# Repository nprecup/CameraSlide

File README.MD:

Automated Camera Slider
=================================================

The goal of this project is to create a budget, yet high quality, motorized camera slider, with two axis capability, and Bluetooth communications. This slider is to be used in very remote locations for time-lapse landscape astrophotography. This drives a requirement for portability, with a small battery and low power consumption.

Mechanical Design
-----------------------

The slide axis is made using two aluminum shafts that serve as rails. A low cost ACME lead screw moves the cart along the axis, driven by a low cost Futaba S3003 servo modified for continuous rotation. The controller can be adapted (without modification to the circuit) for other mechanical drive systems that may be more practical depending on the resources available, including belts or driven rollers. The choice of using hobby servos instead of stepper motors was made clear by the power consumption and complexity requirement. Complex motion profiles are not necessary, and open loop control will work fine. Stepper motors consume too much current, all the time (though the current can be reduced while not moving). Servo motors already have drivers built into them, making it necessary to supply only power and PWM control input. While the open loop control is based upon dead reckoning (timing), rather than by the advantageous simple steps of a stepper motor, the motors can be moved carefully to produce repeatable results. A stepper motor requires additional drive circuitry, increasing cost and complexity.

Circuit Design
-----------------------

This project uses a BlueGiga BLE112 module to control and interface with a motorized camera slide. The BLE112 module contains a 2541 microcontroller that is capable of providing 16-bit resolution PWM output for servo drive signals, hardware interrupt events for limit switches, and timers with GPIO to trigger a camera shutter for time lapse photography. The system is currently being developed for Canon EOS cameras, with an Android app for bluetooth control.

The circuit was designed using Eagle PCB design software. The schematic and board files are located in the repository and may be ordered through any PCB fab shop that can handle Eagle .brd files. Below is the schematic of the circuit.

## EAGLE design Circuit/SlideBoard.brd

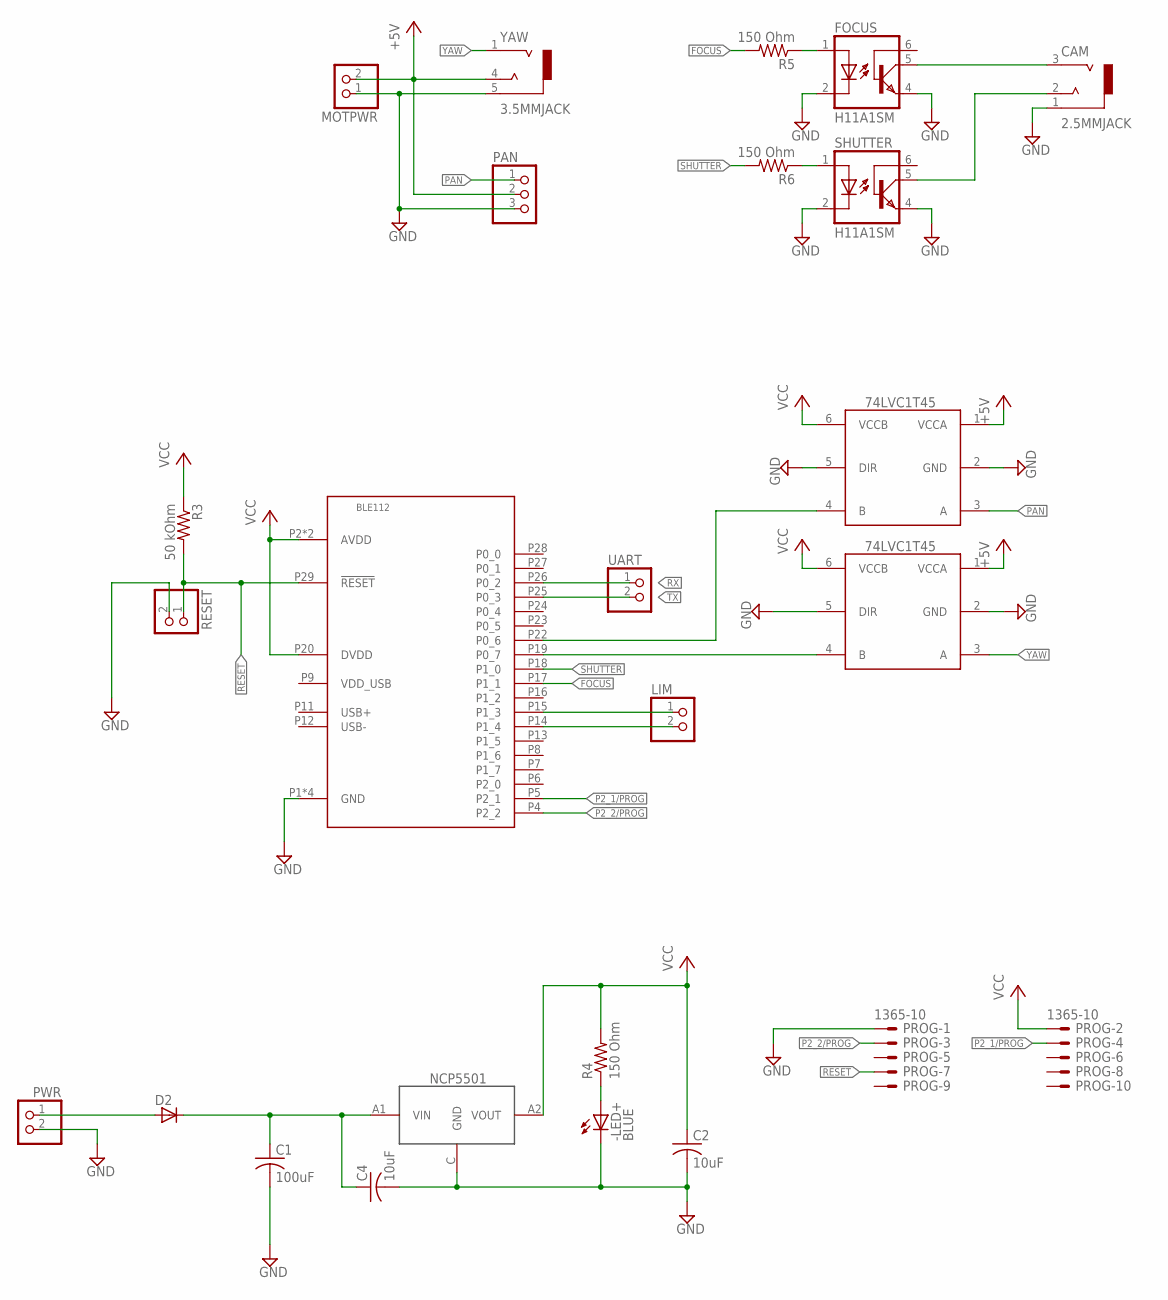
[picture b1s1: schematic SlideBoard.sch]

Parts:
-LED+: BLUE; CHIP-LED0603
C1: 100uF; C1210
C2, C4: 10uF; C0805
CAM: 2.5MMJACK
D2: D-A1-C3; SOT23
FOCUS: H11A1SM; DIL6-SMD
LIM: PINHD-1X2; 1X02
MOTPWR: PINHD-1X2; 1X02
PAN: PINHD-1X3; 1X03
PROG: 1365-10
PWR: PINHD-1X2; 1X02
R3: 50 kOhm; R0603
R4, R5, R6: 150 Ohm; R0402
RESET: PINHD-1X2; 1X02
SHUTTER: H11A1SM; DIL6-SMD
U$1: BLE112
U$2, U$4: 741T45; SOT363_PHILIPS
U$3: NCP5501; DPACK_3
UART: PINHD-1X2; 1X02
YAW: 3.5MMJACK; 35RA_SMT

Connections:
+5V: MOTPWR.2, PAN.2, U$2.1 (VCCA), U$4.1 (VCCA), YAW.4
FOCUS: R5.2, U$1.P17 (P1_1)
GND: -LED+.C, C1.2, C2.2, C4.2, CAM.1 (5-GND), FOCUS.2 (C), FOCUS.4 (EMI), MOTPWR.1, PAN.3, PROG.1, PWR.2, RESET.2, SHUTTER.2 (C), SHUTTER.4 (EMI), U$1.P1 (GND), U$1.P10 (GND), U$1.P21 (GND), U$1.P30 (GND), U$2.2 (GND), U$2.5 (DIR), U$3.C (GND), U$4.2 (GND), U$4.5 (DIR), YAW.5 (5-GND)
unnamed: D2.1 (A), PWR.1
unnamed: FOCUS.1 (A), R5.1
unnamed: R6.1, SHUTTER.1 (A)
unnamed: CAM.2 (4), SHUTTER.5 (COL)
unnamed: CAM.3 (1), FOCUS.5 (COL)
unnamed: LIM.1, U$1.P15 (P1_3)
unnamed: -LED+.A, R4.1
unnamed: LIM.2, U$1.P14 (P1_4)
unnamed: U$1.P19 (P0_7), U$4.4 (B)
unnamed: C1.1, C4.1, D2.3 (C), U$3.A1 (VIN)
P2_1/PROG: PROG.4, U$1.P5 (P2_1)
P2_2/PROG: PROG.3, U$1.P4 (P2_2)
PAN: PAN.1, U$2.3 (A)
RESET: PROG.7, R3.2, RESET.1, U$1.P29 (!RESET)
RX: U$1.P26 (P0_2), UART.1
SHUTTER: R6.2, U$1.P18 (P1_0)
TX: U$1.P25 (P0_3), UART.2
VCC: C2.1, PROG.2, R3.1, R4.2, U$1.P2 (AVDD), U$1.P3 (AVDD), U$1.P20 (DVDD), U$2.6 (VCCB), U$3.A2 (VOUT), U$4.6 (VCCB)
YAW: U$4.3 (A), YAW.1
YAW_LOW: U$1.P22 (P0_6), U$2.4 (B)

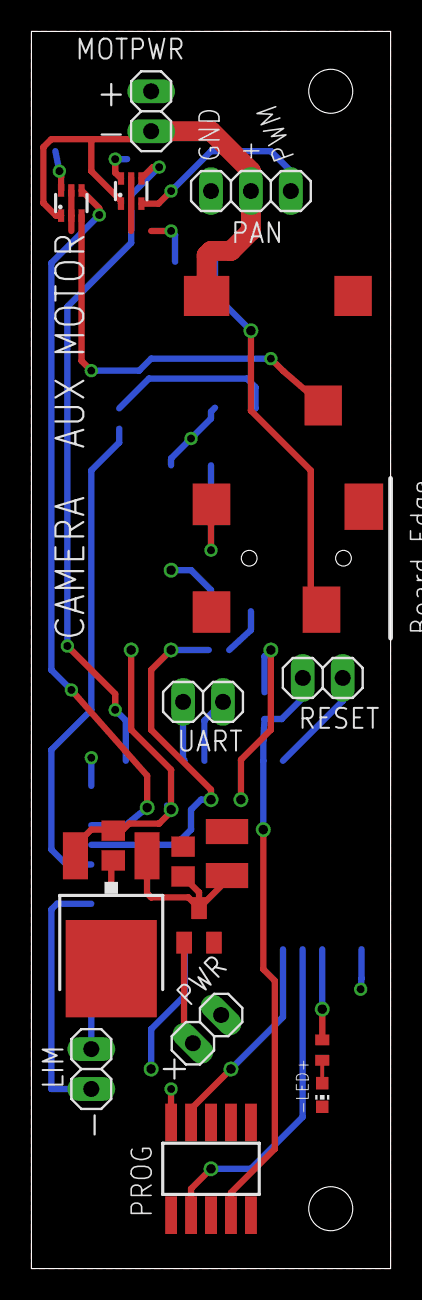
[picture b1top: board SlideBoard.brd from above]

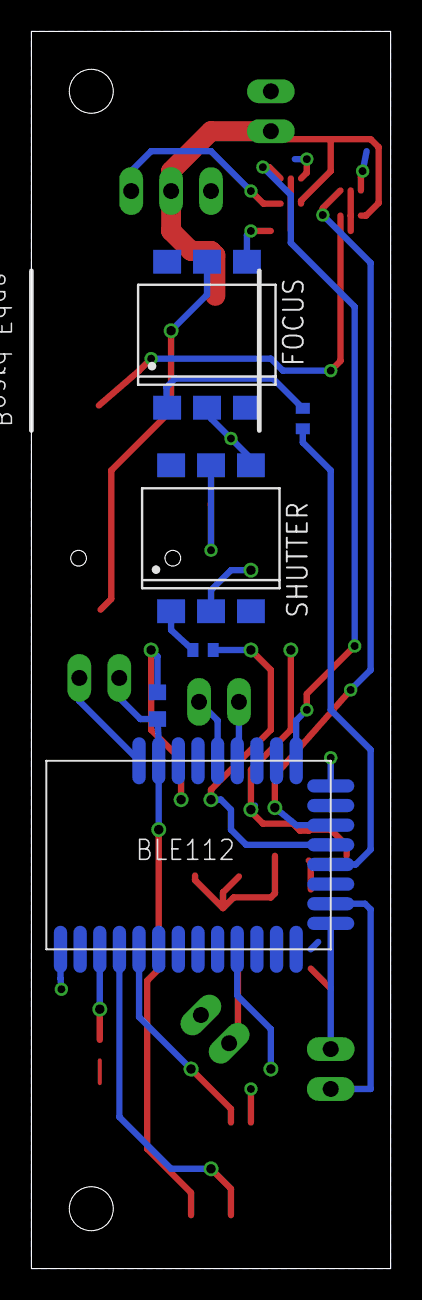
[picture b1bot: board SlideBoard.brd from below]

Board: 2 copper layers, 22.9 x 78.7 mm, 24 parts (6 on the bottom side), 23 nets.

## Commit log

2016-06-14 second commit
2016-06-14 Includes schematic
2016-06-15 Updated readme with information on intended fixes
2016-06-15 Added BGScript code files
2016-06-15 Checked for limits before initializing an axis
2016-06-15 Added notify to characteristic u_init properties
2016-06-15 Updated circuit models to incorporate new changes
2016-06-15 Updates to BGScript
2016-06-15 Added error checking
2016-06-15 Added to do comment on one-shot timer
2016-06-15 Added translational motion between camera shots
2016-06-15 removed old HEX file
2016-06-15 Ready for testing
2016-06-15 Changed all interval and exposure management to one-shot timers for accurate timing
2016-06-15 Fixed error in while loop
2016-06-16 Fixed magic numbers with description
2016-06-16 Removed blocking while loops
2016-06-16 enhanced PWM resolution
2016-06-16 Cleaned up files
2016-06-16 Cleanup
2016-06-16 Added directional capability. Cleaned up limit behavior.
2016-06-16 Icludes encyrypted bonding, and authenticated write attributes
2016-06-19 Added servo tuning functionality
2016-06-19 Change a comment!
    Literally changed a single comment.
2016-06-20 Fixed compile issue with flash memory read command in system boot event
2016-06-20 Several bugfixes and comment changes
    Fixing several bugs from code inspection and review. Tweaking comments
    to reflect what's actually happening.
2016-06-20 Renamed flags for clarity
2016-06-20 Fixed local errors
2016-08-04 Created Android Studio Project
2016-08-05 Adding bluetooth enable in onCreate
2016-08-05 Replaced with example android code
2016-08-05 Removed old android source
2016-08-05 Removed source tarball
2016-08-05 Updated example to studio project
2016-08-26 Updated controller board to include BLE112 for easier soldering
2016-08-27 Updated readme to reflect change to BLE112.
2016-09-13 Removed code causing failure to bond
2016-09-13 Fixed missing power connection
2016-09-14 Fixed ps store bug causing failure during boot
2016-09-15 Updated circuit shematic to reflect current working board version
2016-09-15 Fixed typo
2016-09-15 Updated schematic image file
2016-09-15 removed old schematic
2016-09-17 Updated android test software
